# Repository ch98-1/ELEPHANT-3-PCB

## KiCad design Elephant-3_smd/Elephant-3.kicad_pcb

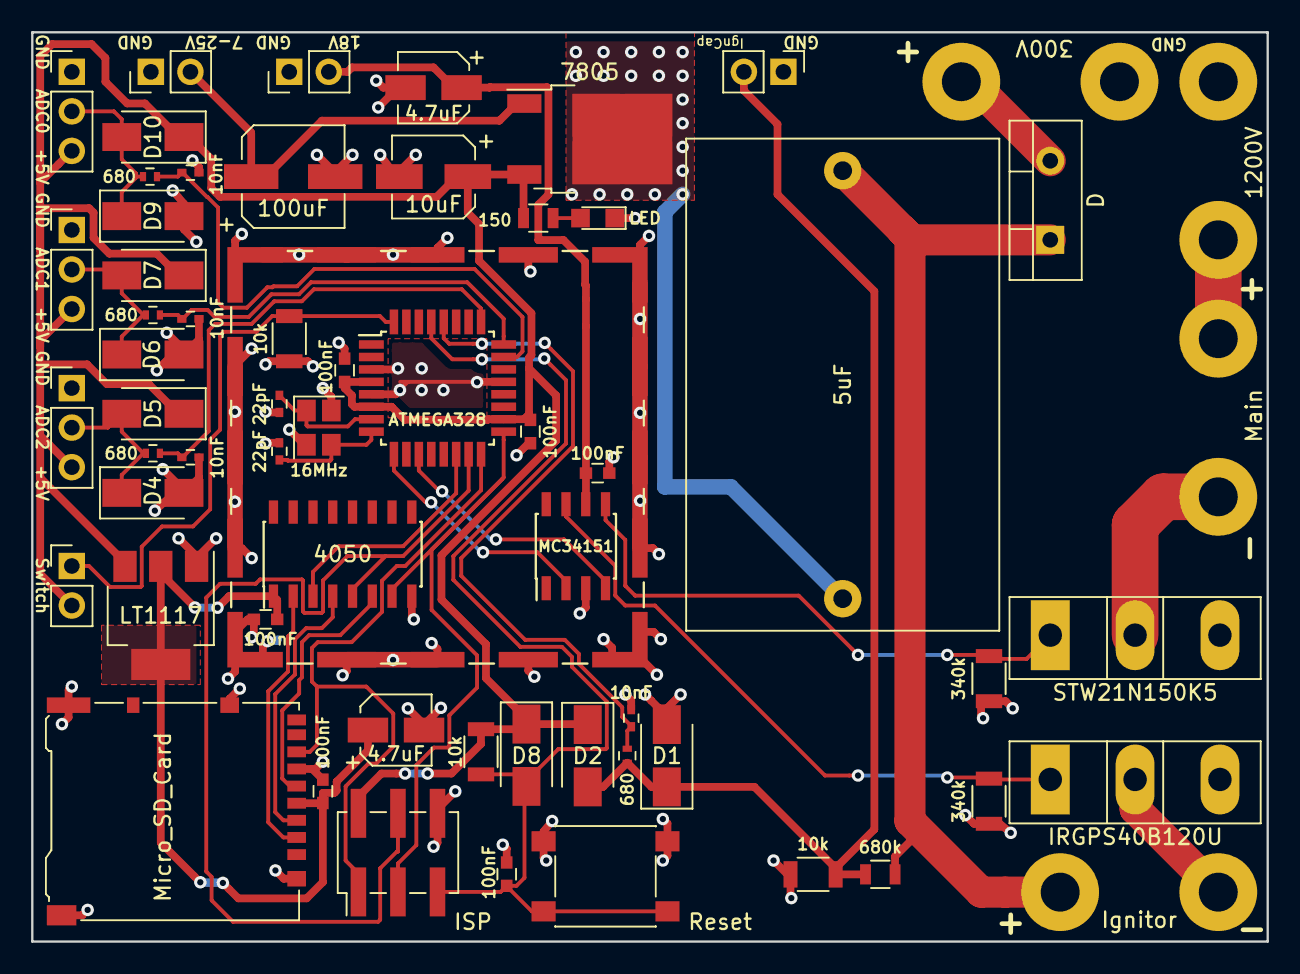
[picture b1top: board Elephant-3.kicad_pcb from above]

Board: 2 copper layers, 79.4 x 58.4 mm, 62 parts (0 on the bottom side), 34 nets.

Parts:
C1, C2, C12, C13, C14, C17: 100nF; C_0603
C3: 100uF; CP_Elec_6.3x5.3
C4, C6, C8, C11: 10nF; C_0402
C5: 10uF; CP_Elec_5x5.3
C7, C15: 4.7uF; CP_Elec_4x5.3
C9, C10: 22pF; C_0402
C16: 5uF; C_Rect_L31.5mm_W20.0mm_P27.50mm_MKS4
CON1: ISP; Pin_Header_Straight_2x03_Pitch2.54mm_SMD
D1, D2, D4, D5, D6, D7, D9, D10: D_Schottky; D_SMA
D3: LED; LED_0805
D8: D; D_SMA
D11: D; TO-220-2_Vertical
J1: 7-25V; Pin_Header_Straight_1x02_Pitch2.54mm
J2: ADC2; Pin_Header_Straight_1x03_Pitch2.54mm
J3: ADC1; Pin_Header_Straight_1x03_Pitch2.54mm
J4: ADC0; Pin_Header_Straight_1x03_Pitch2.54mm
J5: Switch; Pin_Header_Straight_1x02_Pitch2.54mm
J6: 18V; Pin_Header_Straight_1x02_Pitch2.54mm
J7: 300V; HV-WirePad
J8: 1200V; HV-WirePad
J9: Ignitor; HV-WirePad
J10: Micro_SD_Card; Hirose_DM3AT-SF-PEJM5
J11: IgnCap; Pin_Header_Straight_1x02_Pitch2.54mm
J12: Main; HV-WirePad
J13: RF_Shield_Two_Pieces; Laird_Technologies_BMI-S-203-F_26.21x26.21mm
Q1: IRGPS40B120U; TO-247_TO-3P_Vertical
Q2: STW21N150K5; TO-247_TO-3P_Vertical
R1, R3, R4, R7: 680; R_0402
R2: 150; R_0805
R5, R6, R9: 10k; R_1206
R8, R10: 340k; R_1206
R11: 680k; R_0805
SW1: Reset; SW_SPST_PTS645
U1: 7805; TO-252-2
U2: ATMEGA328; TQFP-32_7x7mm_Pitch0.8mm
U3: LT1117; SOT-223-3_TabPin2
U4: MC34151; SOIC-8_3.9x4.9mm_Pitch1.27mm
U5: 4050; SOIC-16_3.9x9.9mm_Pitch1.27mm
Y1: 16MHz; Crystal_SMD_SeikoEpson_FA238-4pin_3.2x2.5mm

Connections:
18V: C14.1, C15.1, J6.2, U4.6
300V: C16.1, D11.1, J9.2, R11.1
1200V: J8.2, J12.2
+3V3: C7.1, C12.1, C17.1, J10.4, U3.2, U5.1
+5V: C1.1, C2.1, C5.1, CON1.2, D2.1, D5.1, D7.1, D8.1, D10.1, J2.3, J3.3, J4.3, J5.2, R2.1, R6.1, U1.3, U2.4, U2.6, U2.18, U3.3
GND: C1.2, C2.2, C3.2, C4.2, C5.2, C6.2, C7.2, C8.2, C9.1, C10.1, C11.2, C12.2, C13.1, C14.2, C15.2, C16.2, C17.2, CON1.6, D1.2, D3.1, D4.2, D6.2, D9.2, J1.1, J2.1, J3.1, J4.1, J6.1, J7.1, J8.1, J10.6, J10.11, J11.1, J13.1, Q1.3, Q2.3, R5.1, R8.2, R9.2, R10.2, SW1.2, U1.2, U2.3, U2.5, U2.21, U3.1, U4.3, U5.8, Y1.2, Y1.4
IgnCap: D1.1, D2.2, J11.2, R1.2, R9.1, R11.2
unnamed: C3.1, J1.2, U1.1
unnamed: C4.1, R1.1, U2.28
unnamed: C6.1, R3.1, U2.25
unnamed: C8.1, R4.1, U2.24
unnamed: C9.2, U2.7, Y1.1
unnamed: C10.2, U2.8, Y1.3
unnamed: C11.1, R7.1, U2.23
unnamed: C13.2, CON1.5, D8.2, R6.2, SW1.1, U2.29
unnamed: CON1.1, J10.7, U2.16
unnamed: CON1.3, U2.17, U5.7
unnamed: CON1.4, U2.15, U5.5
unnamed: D3.2, R2.2
unnamed: D4.1, D5.2, J2.2, R3.2
unnamed: D6.1, D7.2, J3.2, R4.2
unnamed: D9.1, D10.2, J4.2, R7.2
unnamed: D11.2, J7.2
unnamed: J5.1, R5.2, U2.32
unnamed: J9.1, Q1.2
unnamed: J10.2, U5.2
unnamed: J10.3, U5.4
unnamed: J10.5, U5.6
unnamed: J12.1, Q2.2
unnamed: Q1.1, R8.1, U4.7
unnamed: Q2.1, R10.1, U4.5
unnamed: U2.9, U4.2
unnamed: U2.11, U4.4
unnamed: U2.14, U5.3

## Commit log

2017-12-12 Created project file
2017-12-13 Made Schemiatic version 1
2017-12-13 few bug fix
2017-12-13 Updated capacitor value
2017-12-13 Wrong placement of capacitor
2017-12-13 ignoring mac files
2017-12-13 Added micro SD slot
2017-12-14 Added component list and schematic pdf
2017-12-14 Generated netlist
2017-12-14 Layd out all components
2017-12-14 Changed Floodfill
2017-12-14 Proper board outline
2017-12-14 Routed through hole pcb
2017-12-14 Gerber Export Settings
2017-12-14 Finished ground on PCB and generated Gerber
2017-12-15 Updated some tracks
2017-12-15 Fixed some circuit mistakes
2017-12-15 Labeled stuff on PCB
2017-12-29 Added project files for smd version and replaced some component to generic
2017-12-29 Got component list
2017-12-29 Generated netlist for smd
2017-12-29 routed everything except for ground
2017-12-29 Added missing tracks
2017-12-30 Finished routing ground
2017-12-30 Finished Labes
2018-01-01 Removed schimatic pdf
2018-01-03 Added name/version on to pcb
2018-01-11 Fixed incorrect part number
2018-01-12 Switched microcontroller to older vcersion.
    It has less functionarity, and costs more, but we are not using the extra functions and there is better support for older chip for development.
